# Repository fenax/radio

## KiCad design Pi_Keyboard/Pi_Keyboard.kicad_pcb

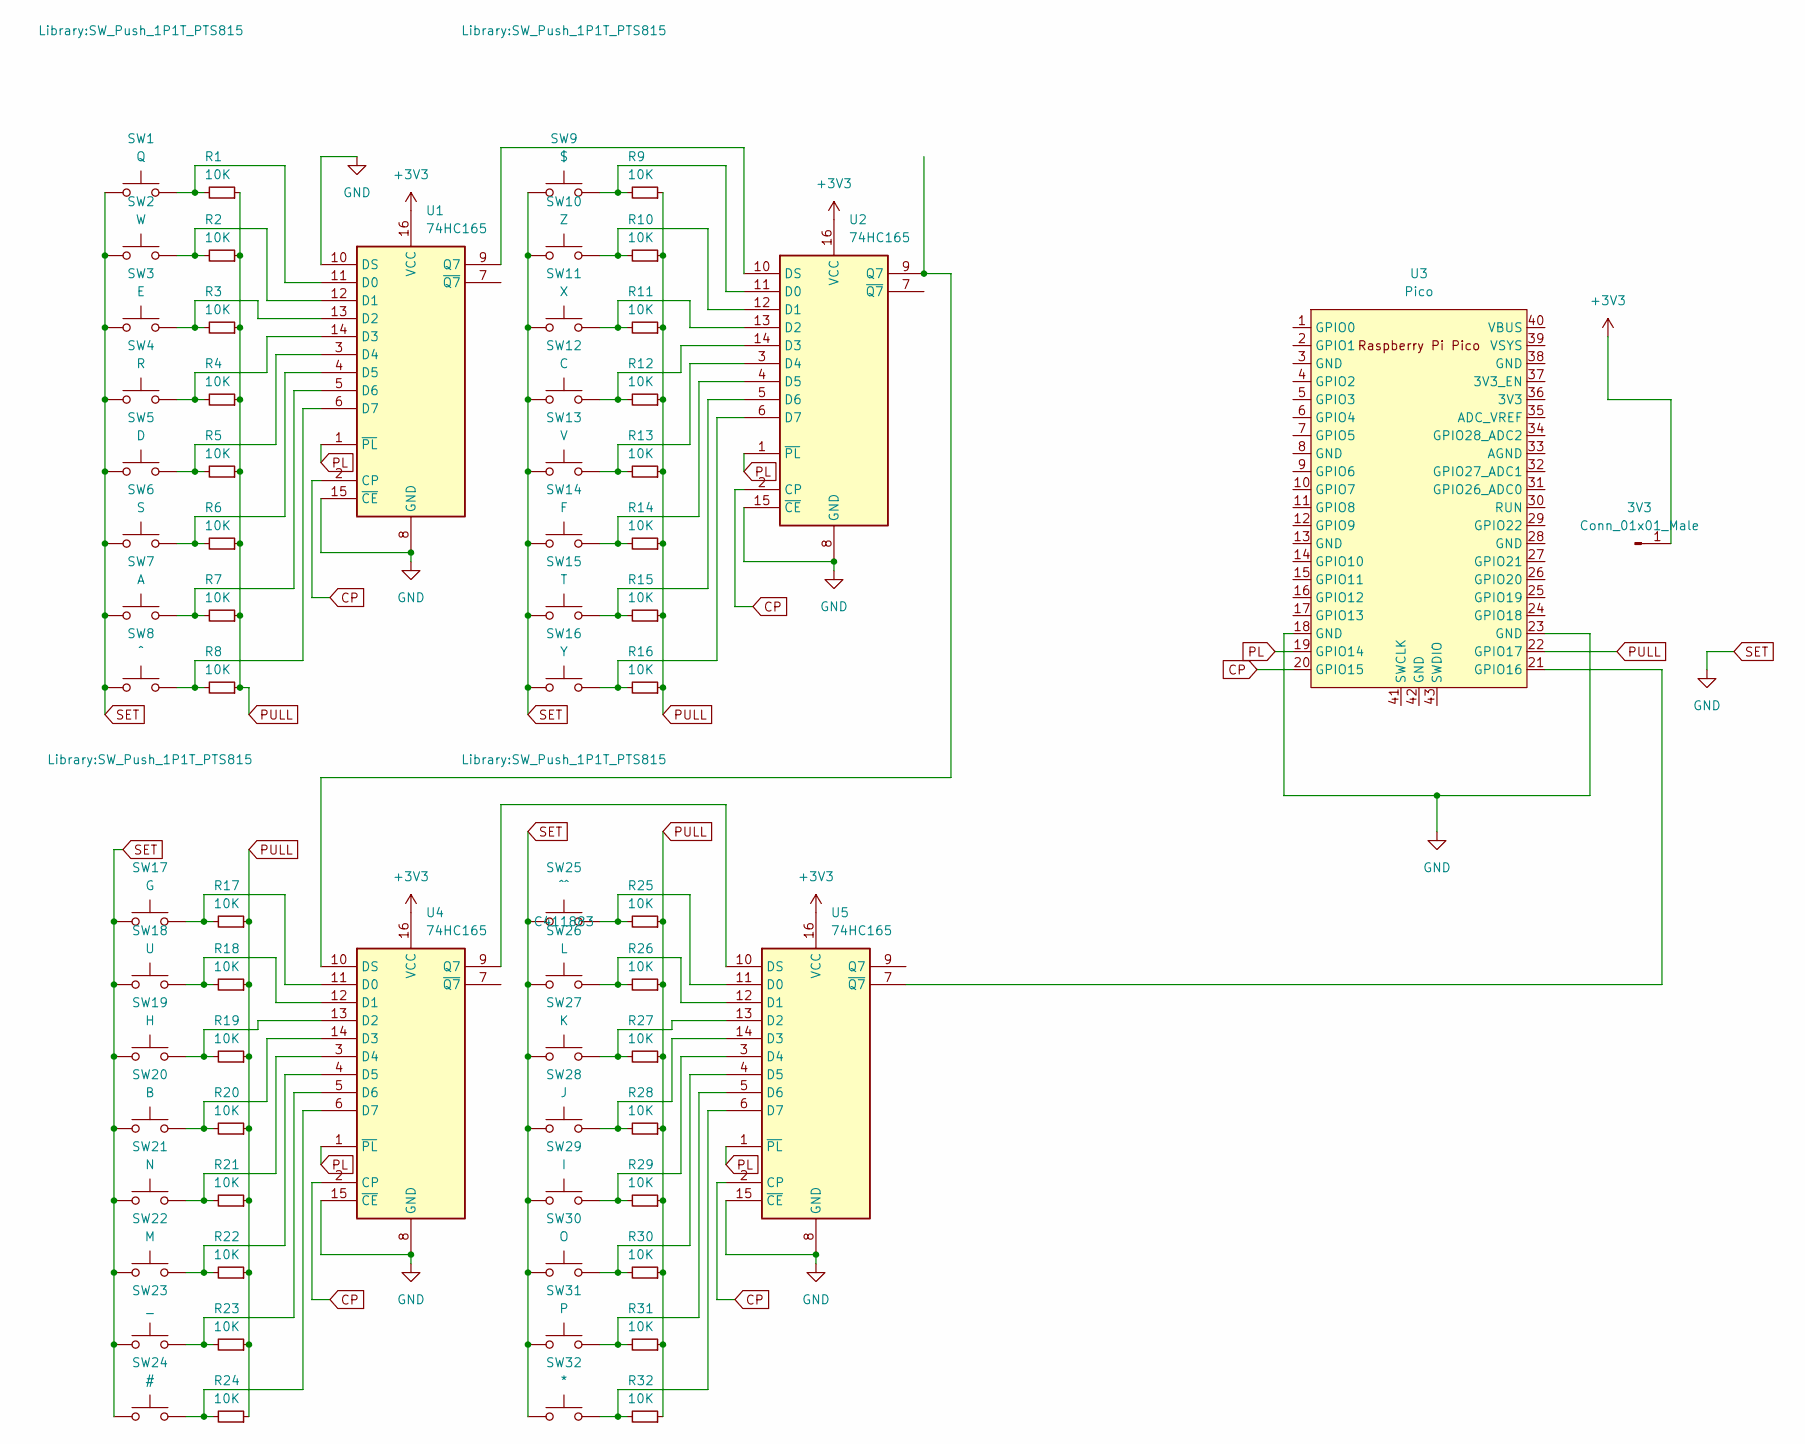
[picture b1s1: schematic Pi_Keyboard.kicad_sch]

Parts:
3V3: Conn_01x01_Male; PinHeader_1x01_P2.54mm_Vertical
R1, R2, R3, R4, R5, R6, R7, R8, R9, R10, R11, R12, R13, R14, R15, R16, R17, R18, R19, R20, R21, R22, R23, R24, R25, R26, R27, R28, R29, R30, R31, R32: 10K; R_0603_1608Metric
SW1: Q; SW_Push_1P1T_PTS815
SW2: W; SW_Push_1P1T_PTS815
SW3: E; SW_Push_1P1T_PTS815
SW4: R; SW_Push_1P1T_PTS815
SW5: D; SW_Push_1P1T_PTS815
SW6: S; SW_Push_1P1T_PTS815
SW7: A; SW_Push_1P1T_PTS815
SW8: ^; SW_Push_1P1T_PTS815
SW9: $; SW_Push_1P1T_PTS815
SW10: Z; SW_Push_1P1T_PTS815
SW11: X; SW_Push_1P1T_PTS815
SW12: C; SW_Push_1P1T_PTS815
SW13: V; SW_Push_1P1T_PTS815
SW14: F; SW_Push_1P1T_PTS815
SW15: T; SW_Push_1P1T_PTS815
SW16: Y; SW_Push_1P1T_PTS815
SW17: G; SW_Push_1P1T_PTS815
SW18: U; SW_Push_1P1T_PTS815
SW19: H; SW_Push_1P1T_PTS815
SW20: B; SW_Push_1P1T_PTS815
SW21: N; SW_Push_1P1T_PTS815
SW22: M; SW_Push_1P1T_PTS815
SW23: _; SW_Push_1P1T_PTS815
SW24: #; SW_Push_1P1T_PTS815
SW25: ^^; SW_Push_1P1T_PTS815; LCSC C411883
SW26: L; SW_Push_1P1T_PTS815
SW27: K; SW_Push_1P1T_PTS815
SW28: J; SW_Push_1P1T_PTS815
SW29: I; SW_Push_1P1T_PTS815
SW30: O; SW_Push_1P1T_PTS815
SW31: P; SW_Push_1P1T_PTS815
SW32: *; SW_Push_1P1T_PTS815
U1, U2, U4, U5: 74HC165; SOIC-16_3.9x9.9mm_P1.27mm
U3: Pico; RPi_Pico_SMD_TH

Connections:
+3V3: 3V3.1, U1.16 (VCC), U2.16 (VCC), U4.16 (VCC), U5.16 (VCC)
CP: U1.2 (CP), U2.2 (CP), U3.20 (GPIO15), U4.2 (CP), U5.2 (CP)
unnamed: R1.2, SW1.1, U1.11 (D0)
unnamed: R2.2, SW2.1, U1.12 (D1)
unnamed: R3.2, SW3.1, U1.13 (D2)
unnamed: R4.2, SW4.1, U1.14 (D3)
unnamed: R5.2, SW5.1, U1.3 (D4)
unnamed: R6.2, SW6.1, U1.4 (D5)
unnamed: R7.2, SW7.1, U1.5 (D6)
unnamed: R8.2, SW8.1, U1.6 (D7)
unnamed: R9.2, SW9.1, U2.11 (D0)
unnamed: R10.2, SW10.1, U2.12 (D1)
unnamed: R11.2, SW11.1, U2.13 (D2)
unnamed: R12.2, SW12.1, U2.14 (D3)
unnamed: R13.2, SW13.1, U2.3 (D4)
unnamed: R14.2, SW14.1, U2.4 (D5)
unnamed: R15.2, SW15.1, U2.5 (D6)
unnamed: R16.2, SW16.1, U2.6 (D7)
unnamed: R17.2, SW17.1, U4.11 (D0)
unnamed: R18.2, SW18.1, U4.12 (D1)
unnamed: R19.2, SW19.1, U4.13 (D2)
unnamed: R20.2, SW20.1, U4.14 (D3)
unnamed: R21.2, SW21.1, U4.3 (D4)
unnamed: R22.2, SW22.1, U4.4 (D5)
unnamed: R23.2, SW23.1, U4.5 (D6)
unnamed: R24.2, SW24.1, U4.6 (D7)
unnamed: R25.2, SW25.1, U5.11 (D0)
unnamed: R26.2, SW26.1, U5.12 (D1)
unnamed: R27.2, SW27.1, U5.13 (D2)
unnamed: R28.2, SW28.1, U5.14 (D3)
unnamed: R29.2, SW29.1, U5.3 (D4)
unnamed: R30.2, SW30.1, U5.4 (D5)
unnamed: R31.2, SW31.1, U5.5 (D6)
unnamed: R32.2, SW32.1, U5.6 (D7)
unnamed: U1.9 (Q7), U2.10 (DS)
unnamed: U2.9 (Q7), U4.10 (DS)
unnamed: U3.21 (GPIO16), U5.7 (~Q7)
unnamed: U4.9 (Q7), U5.10 (DS)
PL: U1.1 (~PL), U2.1 (~PL), U3.19 (GPIO14), U4.1 (~PL), U5.1 (~PL)
PULL: R1.1, R2.1, R3.1, R4.1, R5.1, R6.1, R7.1, R8.1, R9.1, R10.1, R11.1, R12.1, R13.1, R14.1, R15.1, R16.1, R17.1, R18.1, R19.1, R20.1, R21.1, R22.1, R23.1, R24.1, R25.1, R26.1, R27.1, R28.1, R29.1, R30.1, R31.1, R32.1, U3.22 (GPIO17)
SET: SW1.2, SW2.2, SW3.2, SW4.2, SW5.2, SW6.2, SW7.2, SW8.2, SW9.2, SW10.2, SW11.2, SW12.2, SW13.2, SW14.2, SW15.2, SW16.2, SW17.2, SW18.2, SW19.2, SW20.2, SW21.2, SW22.2, SW23.2, SW24.2, SW25.2, SW26.2, SW27.2, SW28.2, SW29.2, SW30.2, SW31.2, SW32.2, U1.8 (GND), U1.10 (DS), U1.15 (~CE), U2.8 (GND), U2.15 (~CE), U3.18 (GND), U3.23 (GND), U4.8 (GND), U4.15 (~CE), U5.8 (GND), U5.15 (~CE)

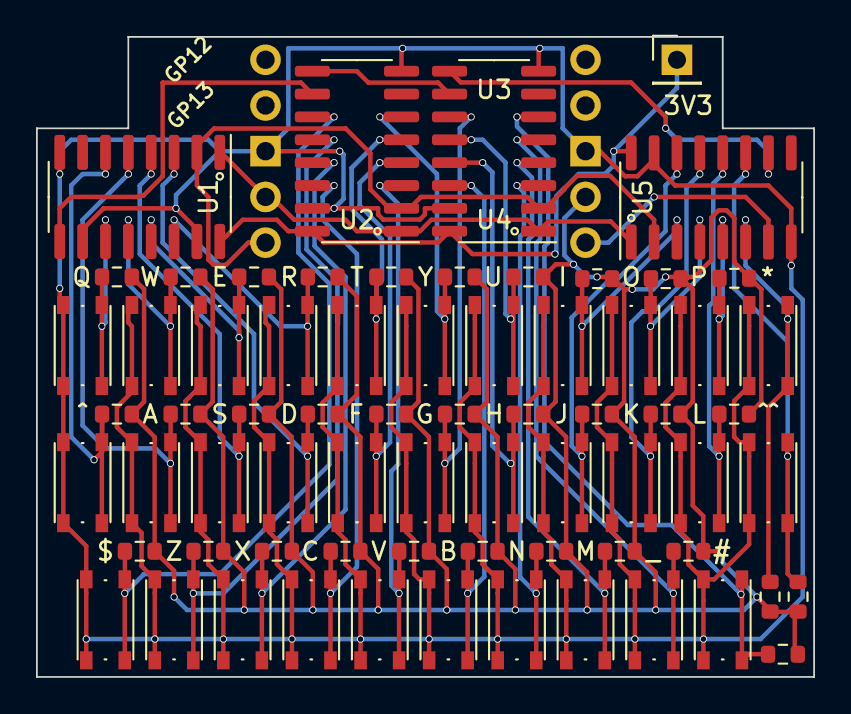
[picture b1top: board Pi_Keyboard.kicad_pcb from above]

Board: 2 copper layers, 43.2 x 35.6 mm, 70 parts (0 on the bottom side), 41 nets.

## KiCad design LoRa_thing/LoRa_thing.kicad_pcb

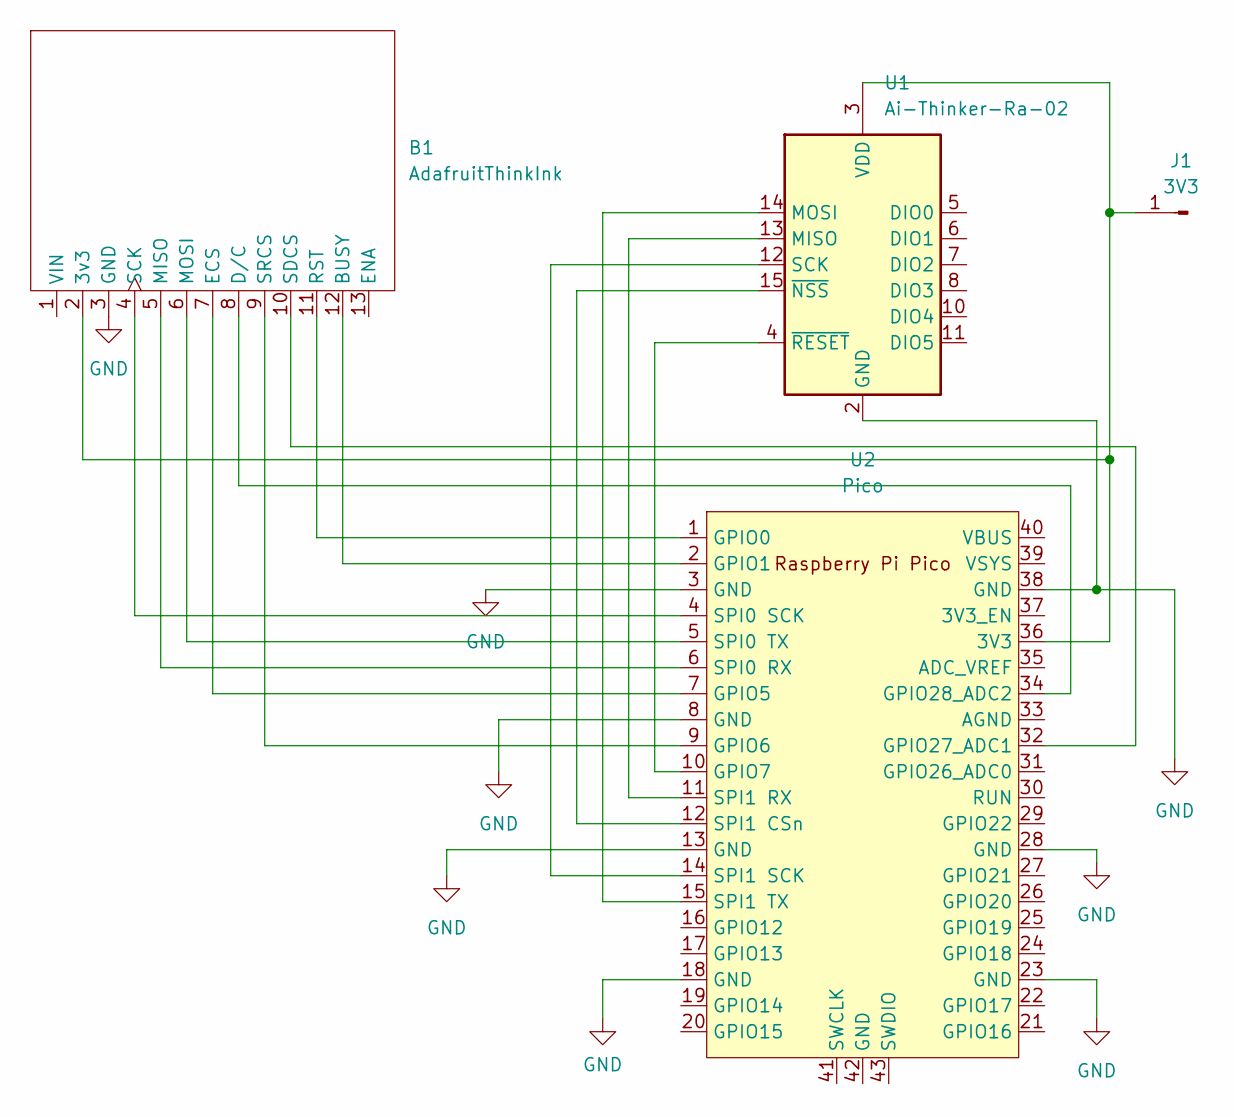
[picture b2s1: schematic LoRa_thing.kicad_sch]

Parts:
B1: AdafruitThinkInk; Adafruit ThinkInk Tricolor 200
J1: 3V3; PinHeader_1x01_P2.54mm_Vertical
U1: Ai-Thinker-Ra-02; DIP-16_RA_02
U2: Pico; RPi_Pico_SMD_TH

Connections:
GND: B1.3 (GND), U1.1 (GND), U1.2 (GND), U1.9 (GND), U1.16 (GND), U2.3 (GND), U2.8 (GND), U2.13 (GND), U2.18 (GND), U2.23 (GND), U2.28 (GND), U2.38 (GND)
unnamed: B1.2 (3v3), J1.1, U1.3 (VDD), U2.36 (3V3)
unnamed: B1.4 (SCK), U2.4 (SPI0 SCK)
unnamed: B1.5 (MISO), U2.6 (SPI0 RX)
unnamed: B1.6 (MOSI), U2.5 (SPI0 TX)
unnamed: B1.7 (ECS), U2.7 (GPIO5)
unnamed: B1.8 (D/C), U2.34 (GPIO28_ADC2)
unnamed: B1.9 (SRCS), U2.9 (GPIO6)
unnamed: B1.10 (SDCS), U2.32 (GPIO27_ADC1)
unnamed: B1.11 (RST), U2.1 (GPIO0)
unnamed: B1.12 (BUSY), U2.2 (GPIO1)
unnamed: U1.4 (~RESET), U2.10 (GPIO7)
unnamed: U1.12 (SCK), U2.14 (SPI1 SCK)
unnamed: U1.13 (MISO), U2.11 (SPI1 RX)
unnamed: U1.14 (MOSI), U2.15 (SPI1 TX)
unnamed: U1.15 (~NSS), U2.12 (SPI1 CSn)

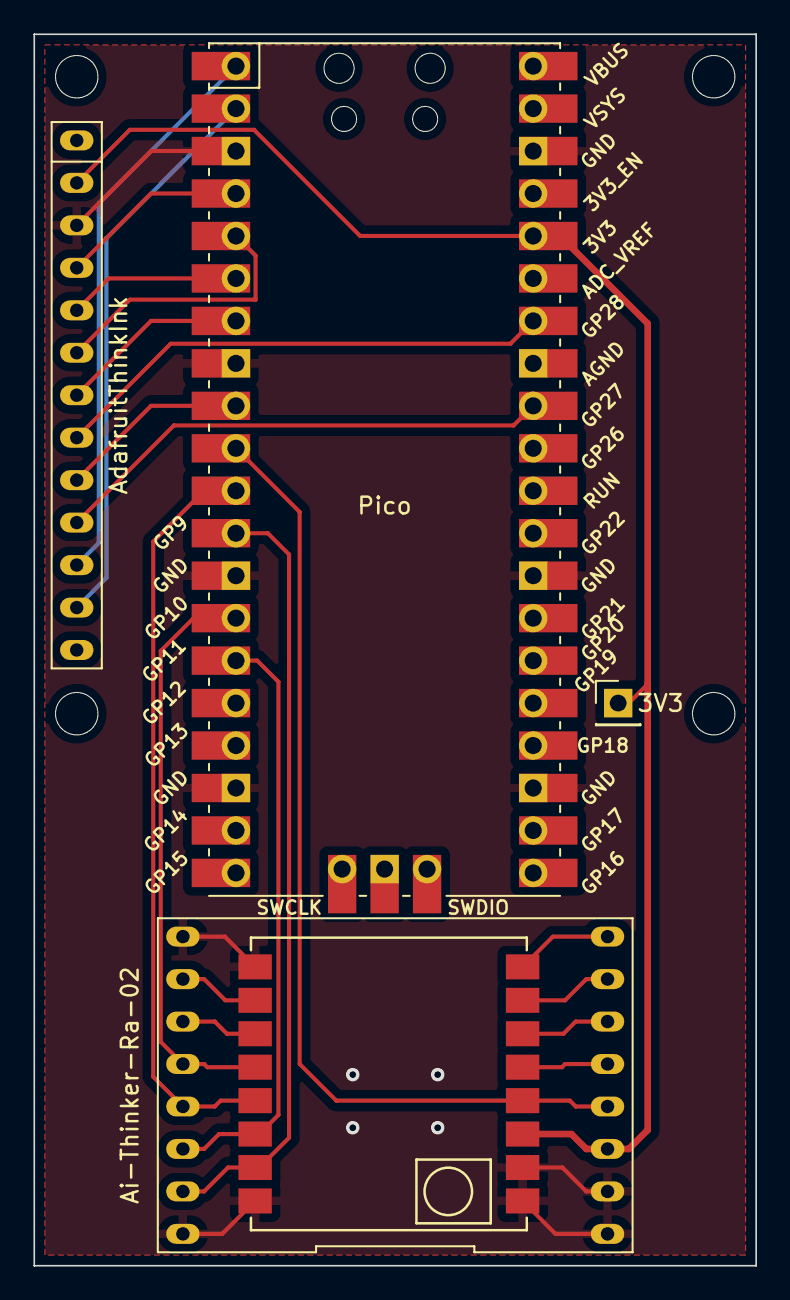
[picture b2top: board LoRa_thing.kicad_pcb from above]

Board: 2 copper layers, 43.2 x 73.7 mm, 4 parts (0 on the bottom side), 16 nets.

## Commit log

2022-09-05 initial
2022-09-06 un peu de travail
2022-09-09 some
